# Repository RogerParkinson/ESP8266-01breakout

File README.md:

# ESP8266-01breakout
Breadboard friendly breakout for an ESP8266-01.
Just the Eagle files for a simple breakout.
It is also shared at [OSHPark](https://www.oshpark.com/shared_projects/v4kTeLxw)
See my [blog post](http://madurasoftware.com/?p=777) for more details.

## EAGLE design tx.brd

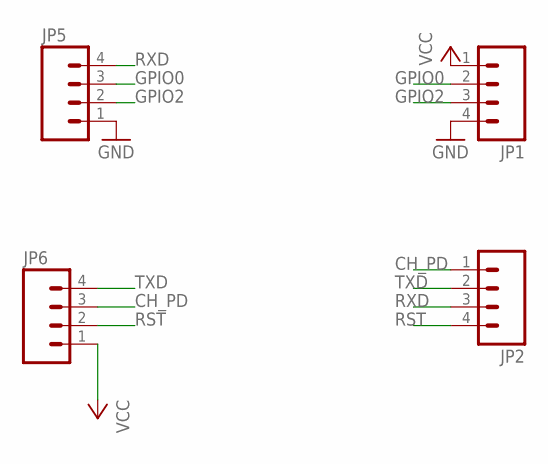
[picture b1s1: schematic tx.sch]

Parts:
JP1, JP2: M04PTH; 1X04
JP5, JP6: M041X04_NO_SILK; 1X04_NO_SILK

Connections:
CH_PD: JP2.1, JP6.3
GND: JP1.4, JP5.1
GPIO0: JP1.2, JP5.3
GPIO2: JP1.3, JP5.2
RST: JP2.4, JP6.2
RXD: JP2.3, JP5.4
TXD: JP2.2, JP6.4
VCC: JP1.1, JP6.1

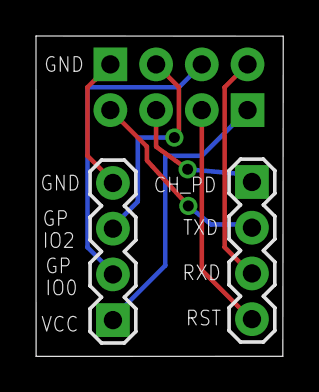
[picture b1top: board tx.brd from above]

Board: 2 copper layers, 13.7 x 17.8 mm, 4 parts (0 on the bottom side), 8 nets.

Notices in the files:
tx.brd:
(c) 2016 Roger Parkinson
parts and their libraries:
SparkFun-Connectors: Licensing: Creative Commons ShareAlike 4.0 International - https://creativecommons.org/licenses/by-sa/4.0
